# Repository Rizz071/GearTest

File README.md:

# GearTest

**Тестовый стенд для 3D-печатных шестерёнок**

---

## 🎯 О проекте

**GearTest** — это полностью открытый тестовый стенд, предназначенный для **испытания 3D-печатных шестерёнок на износ до полного отказа**.

**Главная цель**: довести пару шестерён до разрыва зацепления зубьев и точно зафиксировать момент разрушения с подробным **логированием всех параметров** в десктопное приложение на ПК.

Это позволяет объективно сравнивать долговечность разных материалов (PLA, PETG, ABS, ASA, Nylon и др.), профилей зубьев, параметров печати и постобработки.

---

## ✨ Ключевые возможности

- ✅ Автоматическая остановка при разрушении зацепления  
- ✅ Точный подсчёт времени работы до отказа  
- ✅ Логирование в реальном времени (время, нагрузка)  
- ✅ Удобное десктопное приложение для визуализации и анализа  
- ✅ Сохранение отчётов в CSV + построение графиков  
- ✅ Полностью открытый проект (hardware + software + CAD)

---

## 🛠️ Как это работает

1. В стенд устанавливается пара тестируемых шестерён  
2. Приводной мотор запускает непрерывное вращение под заданной нагрузкой  
3. Система мониторит параметры в реальном времени  
4. При разрыве зубьев (резкое изменение нагрузки/обрыв зацепления) испытание останавливается автоматически  
5. Все данные мгновенно сохраняются и отображаются в приложении на ПК

---

## 📁 Структура репозитория

```bash
GearTest/
├── CAD/          # 3D-модели стенда и шестерёнок
├── Docs/         # Полная документация, схемы, методика испытаний
├── GearTest/     # Исходный код
├── images/       # Фото и скриншоты
├── results/      # Примеры протоколов испытаний (появится позже)
└── LICENSE       # GNU GPL v3.0

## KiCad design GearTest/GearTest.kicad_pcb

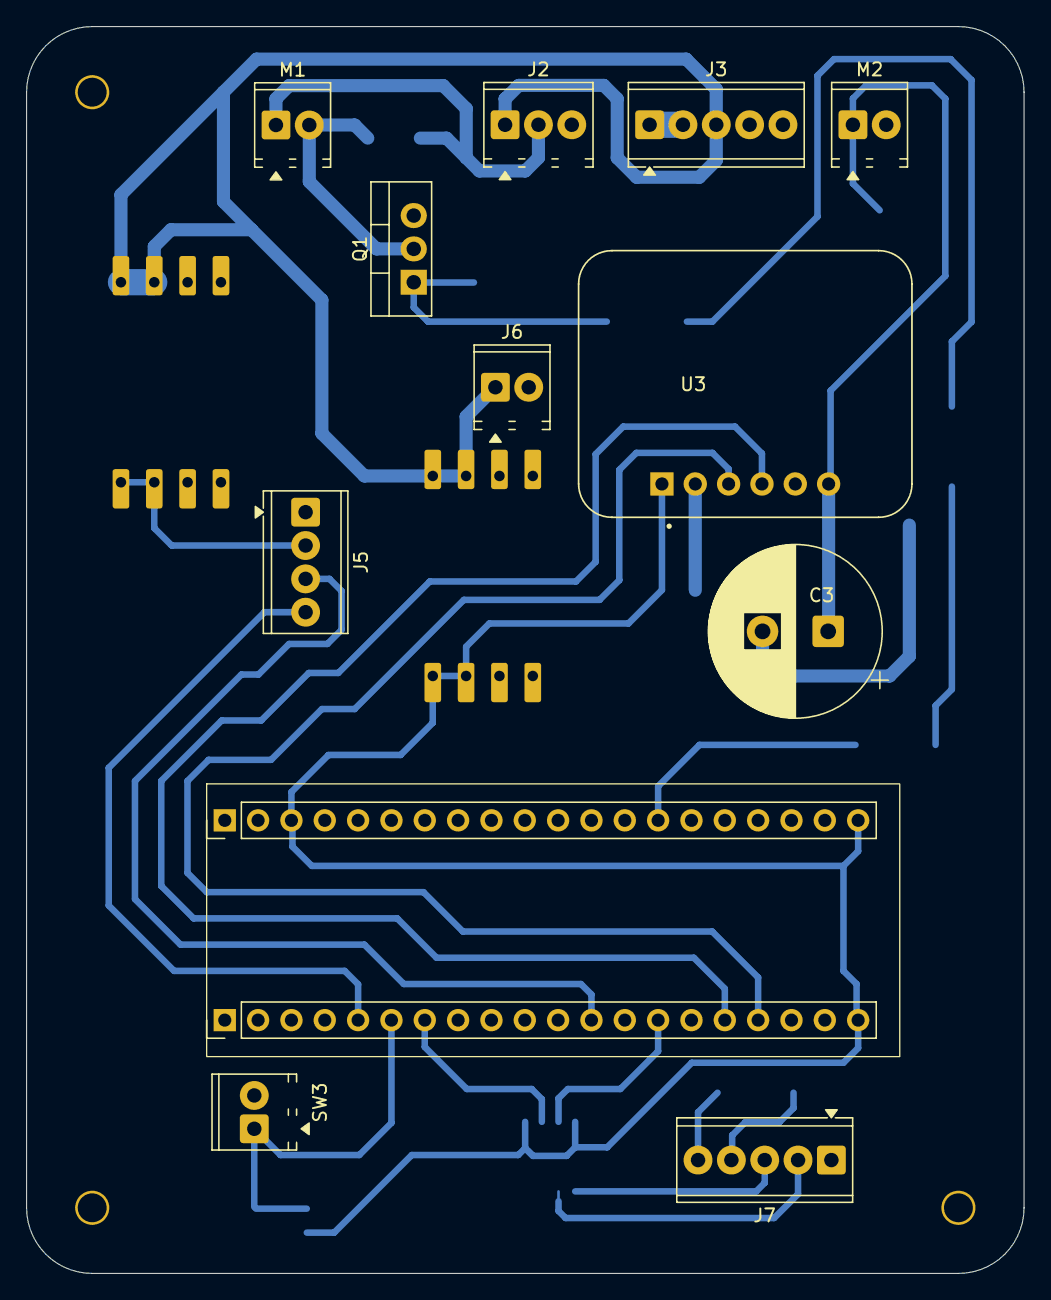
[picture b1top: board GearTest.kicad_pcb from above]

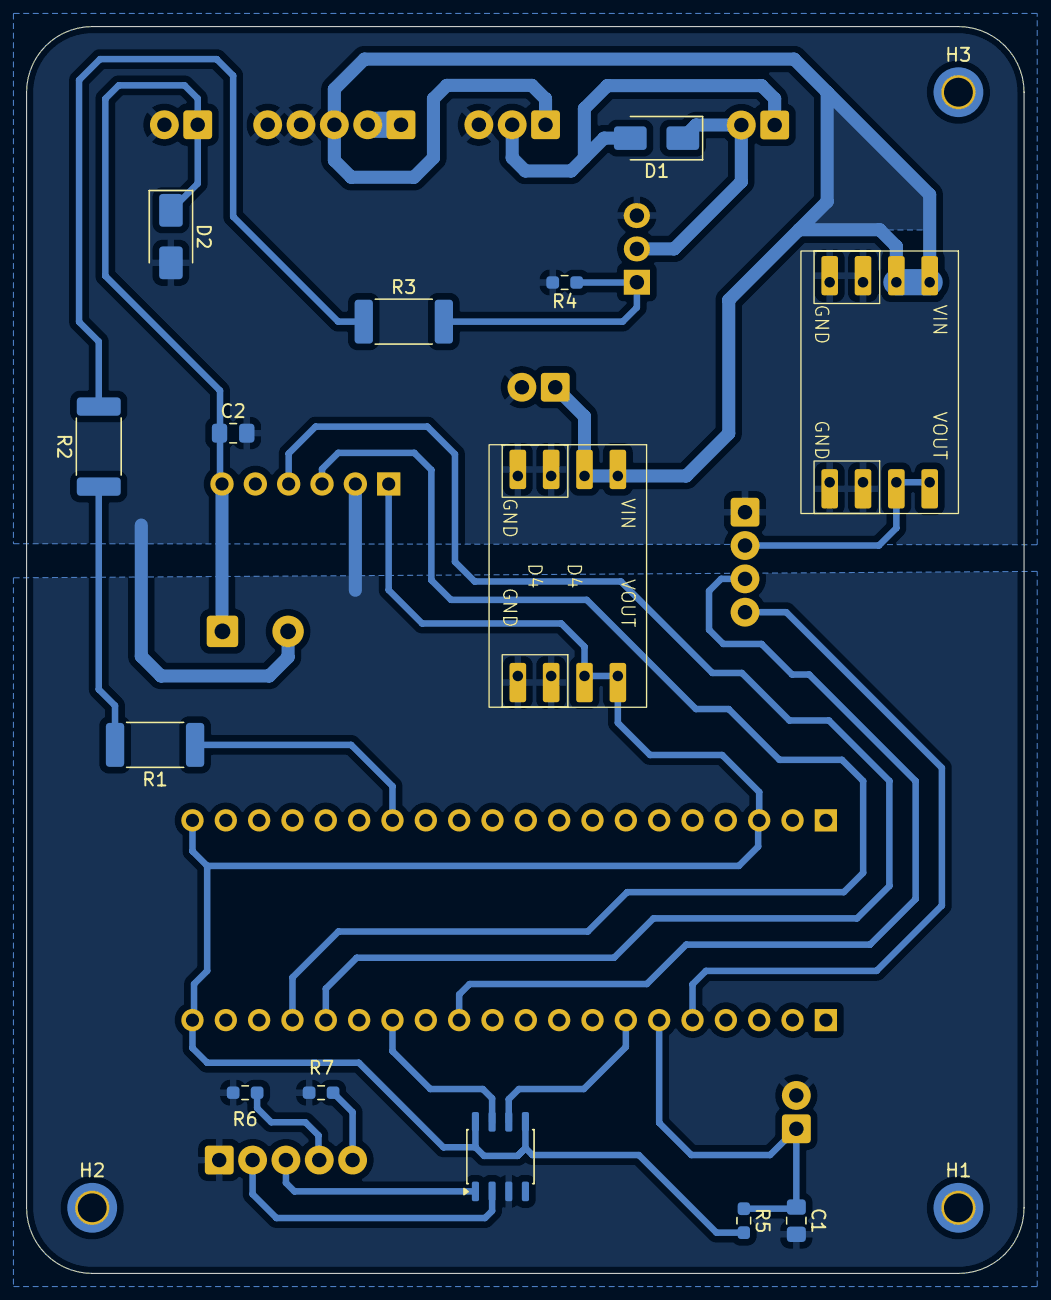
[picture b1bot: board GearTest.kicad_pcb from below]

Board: 2 copper layers, 76.0 x 95.0 mm, 29 parts (17 on the bottom side), 24 nets.

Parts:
C1, C2: 0.1u; C_0805_2012Metric_Pad1.18x1.45mm_HandSolder
C3: 1000u 35М; CP_Radial_D13.0mm_P5.00mm
D1, D2: SS34; D_SMA
D3, D4: WeAct DCM1 LGS5148
H1, H2, H3: MountingHole; MountingHole_2.2mm_M2_DIN965_Pad_TopOnly
J2: Терминал выключателя моторов; TerminalBlock_Phoenix_MPT-0,5-3-2.54_1x03_P2.54mm_Horizontal
J3: Терминал выключателя основного питания; TerminalBlock_Phoenix_MPT-0,5-5-2.54_1x05_P2.54mm_Horizontal
J5: Терминал LCD_1602_I2C; TerminalBlock_Phoenix_MPT-0,5-4-2.54_1x04_P2.54mm_Horizontal
J6: Терминал питания XY-FZ35; TerminalBlock_Phoenix_MPT-0,5-2-2.54_1x02_P2.54mm_Horizontal
J7: Терминал UART1; TerminalBlock_Phoenix_MPT-0,5-5-2.54_1x05_P2.54mm_Horizontal
M1, M2: Motor_DC; TerminalBlock_Phoenix_MPT-0,5-2-2.54_1x02_P2.54mm_Horizontal
Q1: IRLZ44N; TO-220-3_Vertical
R1, R2, R3: 0R; R_2512_6332Metric_Pad1.40x3.35mm_HandSolder
R4, R5: 10k; R_0603_1608Metric_Pad0.98x0.95mm_HandSolder
R6, R7: 5.1k; R_0603_1608Metric_Pad0.98x0.95mm_HandSolder
SW3: SW_Push; TerminalBlock_Phoenix_MPT-0,5-2-2.54_1x02_P2.54mm_Horizontal
U1: WeAct BlackPill STM32F411C_C-E_Ux; WeAct Blackpill
U2: CH340N; JEITA_SOIC-8_3.9x4.9mm_P1.27mm
U3: INA219

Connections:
3V3: D4.3 (VOUT), R5.2, U1.1 (VBAT), U1.60 (3V3), U2.5 (VCC), U2.8 (V3), U3.1 (VCC)
5V0: D3.3 (VOUT), J5.2
12V0: D3.1 (VIN), D4.1 (VIN), J2.1, J3.3, J6.1
/INA219_MOTOR_SCL: U1.45 (PB8), U3.4 (SDA)
/INA219_MOTOR_SDA: U1.46 (PB9), U3.3 (SCL)
/LCD1602_MOTOR_SCL: J5.4, U1.29 (PA8)
/LCD1602_MOTOR_SDA: J5.3, U1.40 (PB4)
/MOTOR_GATE: R1.1, U1.11 (PA1)
/UART1_RX: U1.31 (PA10), U2.6 (TXD)
/UART1_TX: U1.42 (PB6), U2.7 (RXD)
/USB_CC1: J7.4, R6.1
/USB_CC2: J7.5, R7.1
/USB_D+: J7.3, U2.1 (UD+)
/USB_D-: J7.2, U2.2 (UD-)
GNDD: C1.2, D4.4 (GND), J7.1, R6.2, R7.2, SW3.2, U2.3 (GND), U3.2 (GND)
GNDPWR: C2.2, C3.2, D2.2 (A), D3.2 (GND), D3.4 (GND), D4.2 (GND), J2.3, J3.4, J3.5, J5.1, J6.2, M2.2 (-), Q1.3 (S), R4.2
unnamed: D1.2 (A), J2.2, M1.1 (+)
unnamed: D1.1 (K), M1.2 (-), Q1.2 (D)
unnamed: C2.1, C3.1, D2.1 (K), M2.1 (+), U3.6 (VIN+)
unnamed: J3.1, J3.2
unnamed: Q1.1 (G), R3.2, R4.1
unnamed: R1.2, R2.1
unnamed: R2.2, R3.1
unnamed: C1.1, R5.1, SW3.1, U1.30 (PA9)

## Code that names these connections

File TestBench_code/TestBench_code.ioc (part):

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Mcu.Name=STM32F411C(C-E)Ux
Mcu.Package=UFQFPN48
Mcu.UserName=STM32F411CEUx
PA1.GPIOParameters=GPIO_PuPd,GPIO_Label
PA1.GPIO_Label=MOTOR_GATE
PA1.GPIO_PuPd=GPIO_PULLDOWN
PA1.Signal=GPIO_Output
PA10.GPIOParameters=GPIO_Label
PA10.GPIO_Label=UART1_RX
PA10.Mode=Asynchronous
PA10.Signal=USART1_RX
PA13.Mode=Serial_Wire
PA13.Signal=SYS_JTMS-SWDIO
PA14.Mode=Serial_Wire
PA14.Signal=SYS_JTCK-SWCLK
PA8.GPIOParameters=GPIO_Label
PA8.GPIO_Label=LCD1602_MOTOR_SCL
PA8.Mode=I2C
PA8.Signal=I2C3_SCL
PA9.GPIOParameters=GPIO_Label
PA9.GPIO_Label=START_MEASURE_BUTTON
PA9.Signal=GPIO_Input
PB4.GPIOParameters=GPIO_Label
PB4.GPIO_Label=LCD1602_MOTOR_SDA
PB4.Mode=I2C
PB4.Signal=I2C3_SDA
PB6.GPIOParameters=GPIO_Label
PB6.GPIO_Label=UART1_TX
PB6.Mode=Asynchronous
PB6.Signal=USART1_TX
PB8.GPIOParameters=GPIO_Label
PB8.GPIO_Label=INA219_MOTOR_SCL
PB8.Mode=I2C
PB8.Signal=I2C1_SCL
PB9.GPIOParameters=GPIO_Label
PB9.GPIO_Label=INA219_MOTOR_SDA
PB9.Mode=I2C
PB9.Signal=I2C1_SDA
PC14-OSC32_IN.Mode=LSE-External-Oscillator
PC14-OSC32_IN.Signal=RCC_OSC32_IN
PC15-OSC32_OUT.Mode=LSE-External-Oscillator
PC15-OSC32_OUT.Signal=RCC_OSC32_OUT
PH0\ -\ OSC_IN.Mode=HSE-External-Oscillator
PH0\ -\ OSC_IN.Signal=RCC_OSC_IN
PH1\ -\ OSC_OUT.Mode=HSE-External-Oscillator
PH1\ -\ OSC_OUT.Signal=RCC_OSC_OUT
RCC.HSE_VALUE=25000000
RCC.SYSCLKFreq_VALUE=16000000
board=custom

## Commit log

2026-02-07 init repo
2026-03-11 Create README.md with project overview and structure
    Added a README file with project details and structure.
